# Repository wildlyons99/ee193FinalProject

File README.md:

## Here lies the Final Project Work of Tom Lyons, Philip Lengyel, adn Eddy Zhang

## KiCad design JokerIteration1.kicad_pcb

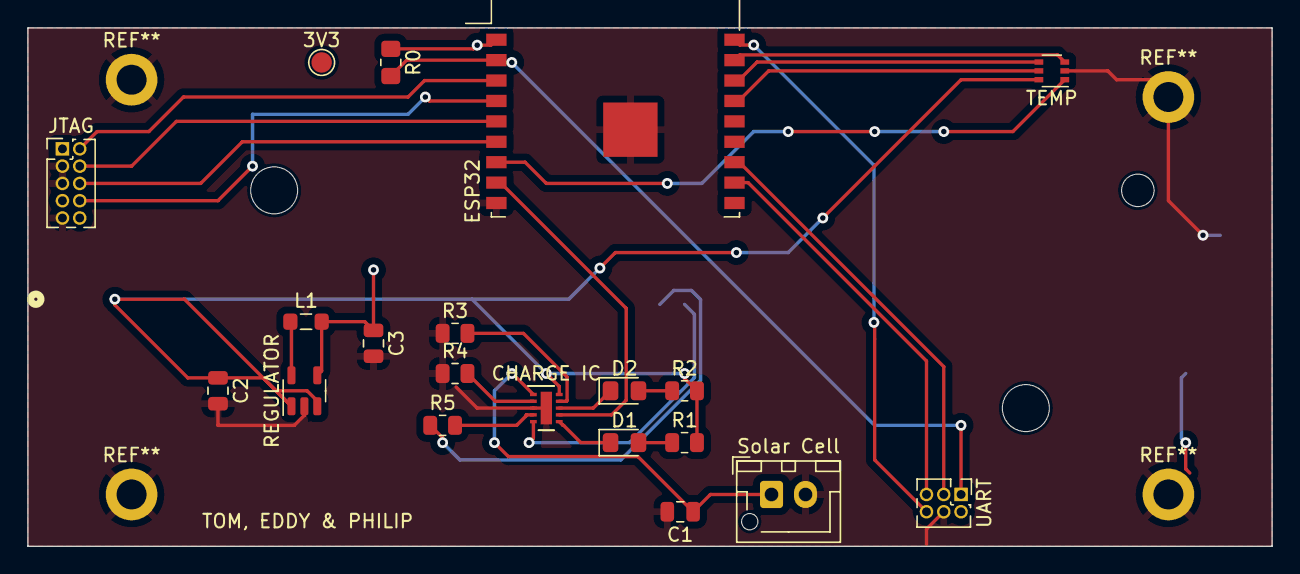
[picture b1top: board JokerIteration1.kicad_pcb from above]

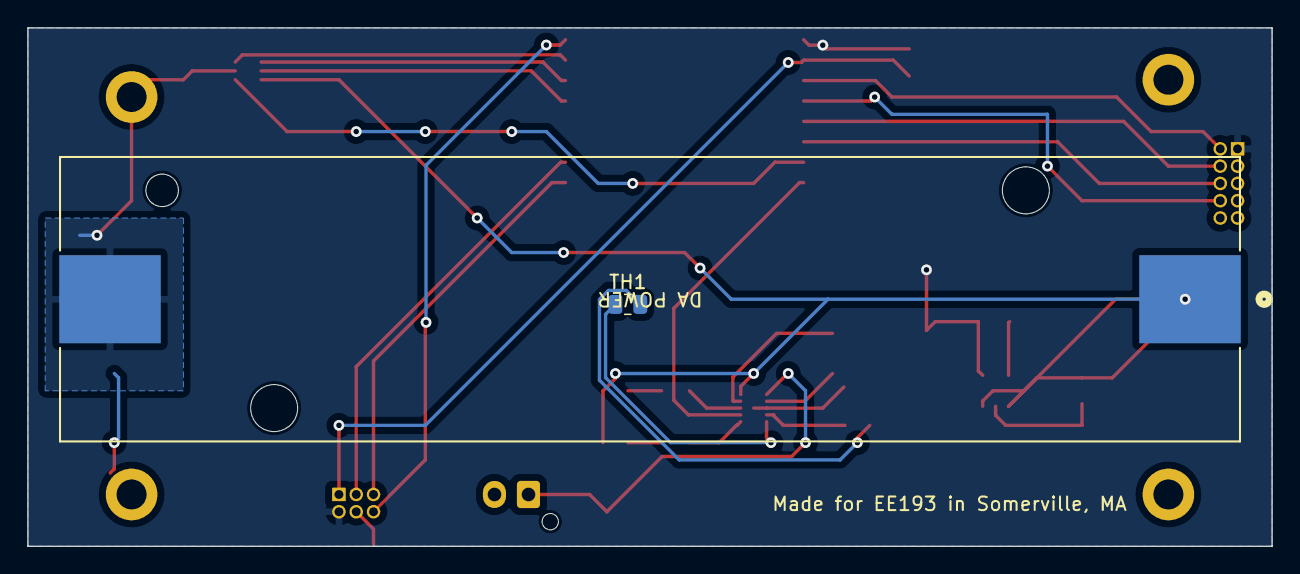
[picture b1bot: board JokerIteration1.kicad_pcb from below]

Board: 2 copper layers, 91.4 x 38.1 mm, 22 parts (2 on the bottom side), 27 nets.

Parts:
3V3: TestPoint_Pad_D1.5mm
C1: 1 uF; C_0805_2012Metric
C2: 4.7 uF; C_0805_2012Metric
C3: 10 uF; C_0805_2012Metric
CHARGE IC: BQ24210DQCR; WSON-10-1EP_2x3mm_P0.5mm_EP0.84x2.4mm
D1, D2: LED; D_0805_2012Metric_Pad1.15x1.40mm_HandSolder
DA POWER: Battery_Cell; 1042P_KEY
ESP32: ESP32-C3-WROOM-02-N4; ESP-WROOM-02
JTAG: Conn_ARM_JTAG_SWD_10; PinHeader_2x05_P1.27mm_Vertical
L1: 10 uF; L_0805_2012Metric_Pad1.05x1.20mm_HandSolder
R0: R; R_0805_2012Metric_Pad1.20x1.40mm_HandSolder
R1: 220 kΩ; R_0805_2012Metric
R2: 220KΩ; R_0805_2012Metric
R3, R4, R5: R; R_0805_2012Metric
REGULATOR: LM3670MF; TSOT-23-5
Solar Cell: Solar_Cell; JST_XH_B2B-XH-AM_1x02_P2.50mm_Vertical
TEMP: TMP126NDCKR; SOT-363_SC-70-6
TH1: Thermistor; R_0805_2012Metric
UART: Conn_02x03_Counter_Clockwise; PinHeader_2x03_P1.27mm_Vertical

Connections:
Battery in: C2.1, CHARGE IC.10 (BAT), DA POWER.1 (+), R1.2, R2.2, REGULATOR.1 (Vin), REGULATOR.3 (EN), TEMP.6 (VDD)
GND: C1.2, C2.2, C3.2, CHARGE IC.3 (VSS), CHARGE IC.11 (EPAD), DA POWER.2 (-), ESP32.9 (GND), ESP32.19 (GND), JTAG.3 (GND), JTAG.5 (GND), JTAG.9 (GND), R3.1, R4.1, REGULATOR.2 (GND), Solar Cell.2 (-), TEMP.2 (GND), UART.4
unnamed: D1.2 (A), R1.1
unnamed: CHARGE IC.6 (*PG), D1.1 (K)
unnamed: D2.2 (A), R2.1
unnamed: CHARGE IC.8 (*CHG), D2.1 (K)
unnamed: ESP32.5 (IO6), JTAG.4 (ESP_TCK)
unnamed: ESP32.4 (IO5), JTAG.8 (ESP_TDI)
unnamed: ESP32.6 (IO7), JTAG.6 (ESP_TDO)
unnamed: ESP32.3 (IO4), JTAG.2 (ESP_TMS)
unnamed: ESP32.2 (EN), R0.2, UART.1
unnamed: ESP32.18 (IO0), UART.6
unnamed: R5.1, TH1.2
unnamed: C1.1, CHARGE IC.1 (VBUS), Solar Cell.1 (+)
unnamed: ESP32.15 (IO3), TEMP.5 (*ALERT)
unnamed: ESP32.7 (IO8), TEMP.1 (*CS)
unnamed: ESP32.16 (IO2), TEMP.4 (SCLK)
unnamed: ESP32.17 (IO1), TEMP.3 (SIO)
unnamed: CHARGE IC.7 (*EN), ESP32.8 (IO9)
unnamed: CHARGE IC.2 (ISET), R4.2
unnamed: CHARGE IC.5 (TS), TH1.1
unnamed: CHARGE IC.9 (VDPM), R3.2
unnamed: CHARGE IC.4 (VTSB), R5.2
unnamed: L1.1, REGULATOR.5 (SW)
UART RX: ESP32.11 (RXD), UART.5
UART TX: ESP32.12 (TXD), UART.3
Vout (LM3670): C3.1, ESP32.1 (3V3), JTAG.1 (VDD), L1.2, R0.1, REGULATOR.4 (FB), UART.2

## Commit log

2024-05-07 intitial code push
2024-05-07 added inital PCB draft
2024-05-07 trying to fix pcb access on git
2024-05-07 add new pcb
2024-05-07 add pcb files
2024-05-10 kinda working?
